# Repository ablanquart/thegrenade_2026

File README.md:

# The Grenade 2026 - An MRF101 40m AM Linear Amplifier
## USB-C Powered - 10W Carrier / 40W PEP - SMA Connectors

A bench-oriented 40-meter (7.0–7.3 MHz) AM linear amplifier built around a push-pull
pair of NXP **MRF101AN/MRF101BN** LDMOS transistors — powered from a standard 100 W
USB-C PD supply. Designed for experimental use under an FCC Part 5 license and
general amateur use on 40m.

**10 W carrier / 40 W PEP · 50 Ω in/out · runs from a laptop brick · absorptive harmonic termination**

## Features

- **USB-C powered**: negotiates 20 V / 5 A from any 100 W PD supply via a CH224K sink
  controller, then boosts to 48 V with an LM5122 synchronous boost converter.
- **Dual power path**: the boost output and a 48 V bench input are diode-ORed onto the
  main VDD rail — plug in whichever you have; both is fine.
- **Absorptive harmonic termination**: a high-pass diplexer branch dumps everything the
  output low-pass filter rejects into a 50 Ω / 6 W resistive load instead of reflecting
  it back into the PA drains. The transistors see a resistive load at all frequencies.
- **Interlocked bring-up**: the driver supply (LM2596HV buck) is enabled only after PD
  negotiation succeeds, or manually via a force-enable jumper (J5).
- **Status LEDs**: green = PD negotiated and boost alive; amber = main 48 V rail present.
- Temperature-tracked gate bias for the output pair.
- 7-element Chebyshev low-pass output filter, 7.5 MHz cutoff.

## Repository layout

```
├── mrf101_40m_pa_usbpd.kicad_pro   # KiCad project
├── mrf101_40m_pa_usbpd.kicad_sch   # Schematic
├── mrf101_40m_pa_usbpd.kicad_pcb   # Board (220 × 130 mm, 2-layer)
├── BOM_mrf101_40m_pa_usbpd.csv     # Bill of materials (grouped, with quantities)
├── fab_usbpd/                      # Gerbers, drill files, paste layers
├── docs/
│   ├── USER_GUIDE.md               # Setup and operation
│   └── SERVICE_MANUAL.md           # Theory of operation, component reference, test points
├── CHANGELOG.md
├── LICENSE                         # CERN-OHL-S v2
└── README.md
```

## Quick start

1. Bolt the board to a heatsink — the MRF101 pair **requires** one (TO-220 tab-down).
2. Connect a 50 Ω dummy load or antenna system to **J2 (RF OUT)**. Never key without a load.
3. Power: plug a 100 W USB-C PD supply into **J4**, or 48 V bench into **J3**.
4. Green LED (D7) = PD negotiated; amber LED (D8) = 48 V rail up.
5. Apply drive (≈1 W nominal) to **J1 (RF IN)**.

Full setup, bias adjustment, and first-power-up procedures are in
[docs/USER_GUIDE.md](docs/USER_GUIDE.md). Circuit theory, a complete component function
reference, and oscilloscope test points are in
[docs/SERVICE_MANUAL.md](docs/SERVICE_MANUAL.md).

## Bill of materials

The complete grouped BOM is [`BOM_mrf101_40m_pa_usbpd.csv`](BOM_mrf101_40m_pa_usbpd.csv).
Sourcing notes for the parts that matter:

| Part | Refs | Notes |
|---|---|---|
| MRF101AN + MRF101BN | Q1, Q2 | Buy the AN/BN *pair* — mirrored pinouts for layout symmetry. |
| CH224K | U3 | USB-PD sink controller, SSOP-10. |
| LM5122 | U4 | Sync boost controller, HTSSOP-20 (exposed pad). |
| LM2596HV-12 | U2 | HV variant is mandatory — input is 48 V. |
| BN-43-202, BN-43-3312 | T1, T2 | Binocular ferrite cores; wind per schematic. |
| 330 pF C0G **250 V** | C33, C34 | Diplexer series caps — voltage rating matters. |
| 390 nH, Q > 50 @ 20 MHz | L8 | 1812 air-core/ceramic, or wind 8t on a T37-6. |
| 100 Ω **3 W** 2512 | R34, R35 | The harmonic dump — do not substitute smaller. |
| USB-C 16-pin receptacle | J4 | Mid-mount, 5 A rated. |

## Regenerating fabrication files

With KiCad 10.x:

```sh
KCLI=/Applications/KiCad/KiCad.app/Contents/MacOS/kicad-cli   # adjust for your OS

$KCLI pcb export gerbers mrf101_40m_pa_usbpd.kicad_pcb -o fab_usbpd/
$KCLI pcb export drill   mrf101_40m_pa_usbpd.kicad_pcb -o fab_usbpd/ \
      --excellon-units mm --excellon-separate-th
```

Include the paste layers (F.Paste/B.Paste) if you're having a stencil made.

## Safety

This is a 40-watt RF power amplifier running on a 48-volt rail. Treat it accordingly:
hot heatsinks, RF voltage on exposed copper, and enough stored energy in the bulk
capacitors to be memorable. Operate into a proper load, within your license privileges,
and keep fingers off the output network while transmitting.

## License

This project is licensed under the **CERN Open Hardware Licence Version 2 —
Strongly Reciprocal (CERN-OHL-S v2)**. See [LICENSE](LICENSE) for the full text.

Copyright © 2026 Adam Blanquart

This source describes Open Hardware and is licensed under the CERN-OHL-S v2.
You may redistribute and modify this source and make products using it under
the terms of the CERN-OHL-S v2 (https://ohwr.org/cern_ohl_s_v2.txt).

This source is distributed WITHOUT ANY EXPRESS OR IMPLIED WARRANTY, INCLUDING
OF MERCHANTABILITY, SATISFACTORY QUALITY AND FITNESS FOR A PARTICULAR PURPOSE.
Please see the CERN-OHL-S v2 for applicable conditions.

Source location: https://github.com/ablanquart/thegrenade_2026/

As per CERN-OHL-S v2 section 4.1, any product you make from this design should
carry a reference back to the source location above.

---

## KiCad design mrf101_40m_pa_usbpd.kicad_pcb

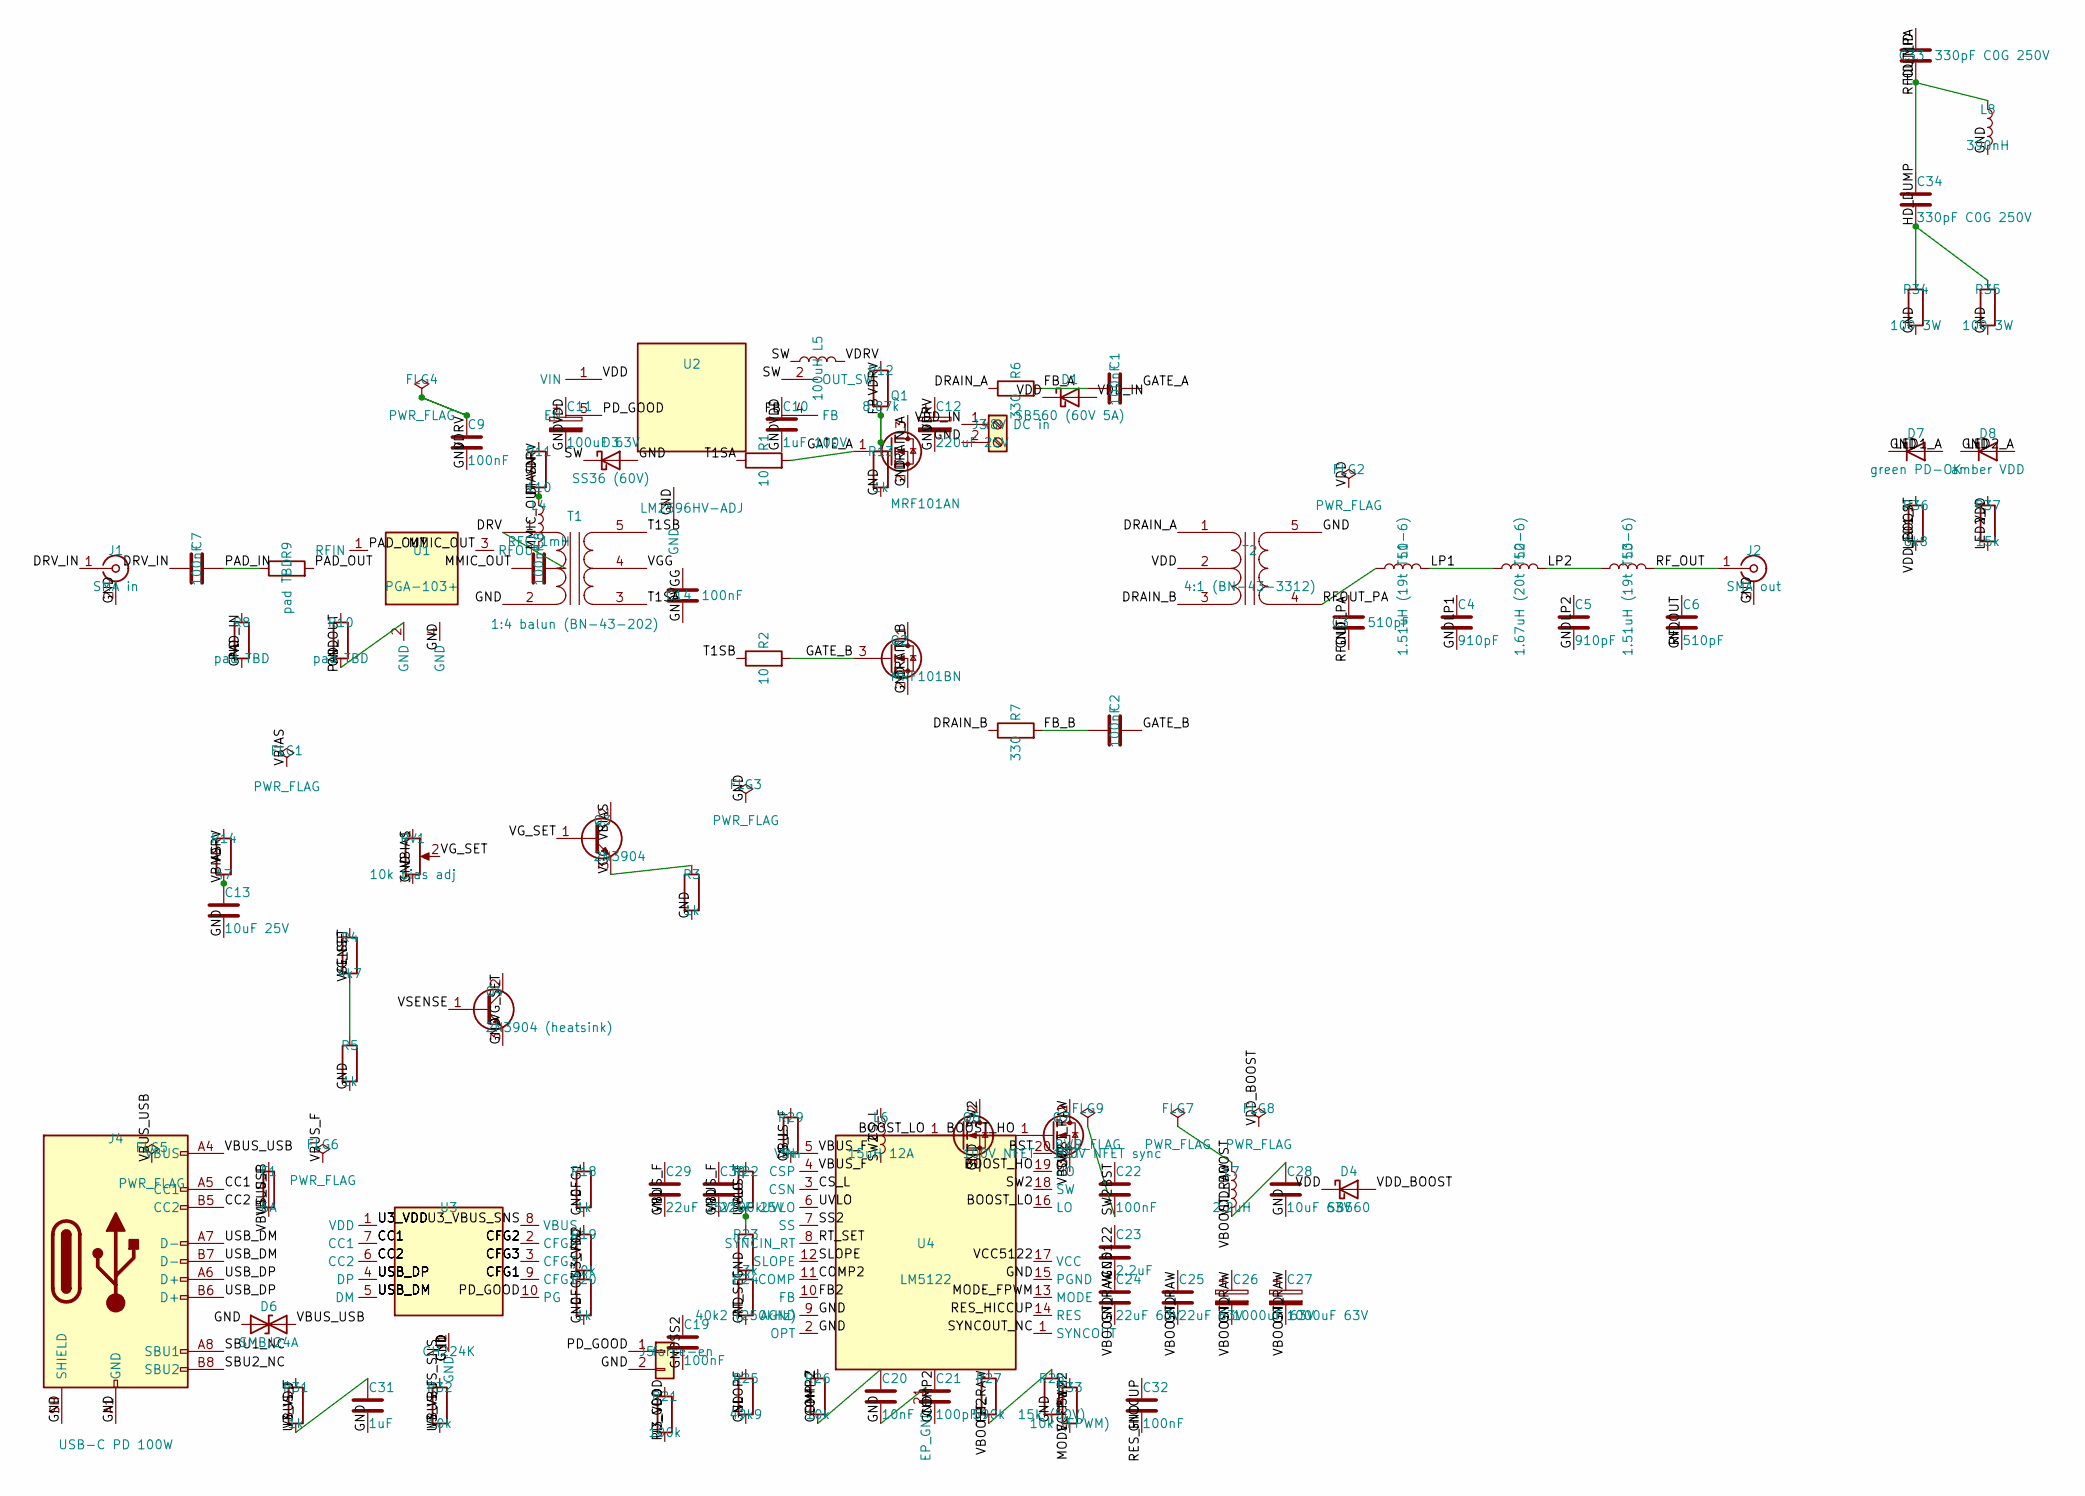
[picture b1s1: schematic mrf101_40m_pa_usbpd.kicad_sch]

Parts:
C1, C2, C7, C8, C9, C14, C19, C22, C32: 100nF; C_0805_2012Metric
C3, C6: 510pF; C_1206_3216Metric
C4, C5: 910pF; C_1206_3216Metric
C10: 1uF 100V; C_1206_3216Metric
C11: 100uF 63V; CP_Radial_D8.0mm_P3.50mm
C12: 220uF 25V; CP_Radial_D8.0mm_P3.50mm
C13: 10uF 25V; C_1206_3216Metric
C20: 10nF; C_0805_2012Metric
C21: 100pF; C_0805_2012Metric
C23: 2.2uF; C_1206_3216Metric
C24, C25: 22uF 63V; C_1210_3225Metric
C26, C27: 1000uF 63V; CP_Radial_D10.0mm_P5.00mm
C28: 10uF 63V; C_1210_3225Metric
C29, C30: 22uF 25V; C_1210_3225Metric
C31: 1uF; C_0805_2012Metric
C33, C34: 330pF C0G 250V; C_1210_3225Metric
D1: SB560 (60V 5A); D_SMC
D3: SS36 (60V); D_SMA
D4: SB560; D_SMC
D6: SMBJ24A; D_SMB
D7: green PD-OK; LED_0805_2012Metric
D8: amber VDD; LED_0805_2012Metric
F1: 6A; Fuse_1812_4532Metric
FLG1, FLG2, FLG3, FLG4, FLG5, FLG6, FLG7, FLG8, FLG9: PWR_FLAG
J1: SMA in; SMA_Molex_73251-1153_EdgeMount_Horizontal
J2: SMA out; SMA_Molex_73251-1153_EdgeMount_Horizontal
J3: 48V DC in; TerminalBlock_MaiXu_MX126-5.0-02P_1x02_P5.00mm
J4: USB-C PD 100W; USB_C_Receptacle_HRO_TYPE-C-31-M-12
J5: force-en; PinHeader_1x02_P2.54mm_Vertical
L1, L3: 1.51uH (19t T50-6); L_Toroid_Vertical_L14.0mm_W6.3mm_P4.57mm_Pulse_A
L2: 1.67uH (20t T50-6); L_Toroid_Vertical_L14.0mm_W6.3mm_P4.57mm_Pulse_A
L4: RFC 1mH; L_Toroid_Vertical_L14.0mm_W6.3mm_P4.57mm_Pulse_A
L5: 100uH; L_12x12mm_H8mm
L6: 15uH 12A; L_12x12mm_H8mm
L7: 2.2uH; L_12x12mm_H4.5mm
L8: 390nH; L_1812_4532Metric
Q1: MRF101AN; TO-220-3_Horizontal_TabDown
Q2: MRF101BN; TO-220-3_Horizontal_TabDown
Q3: 2N3904; TO-92_Inline
Q4: 2N3904 (heatsink); TO-92_Inline
Q6: 100V NFET; TO-252-2
Q7: 100V NFET sync; TO-252-2
R1, R2: 10; R_0805_2012Metric
R3, R5, R13, R18, R20, R31: 1k; R_0805_2012Metric
R4: 4k7; R_0805_2012Metric
R6, R7: 330; R_2512_6332Metric
R8, R9, R10: pad TBD; R_0805_2012Metric
R11: 110; R_0805_2012Metric
R12: 8.87k; R_0805_2012Metric
R14: 47; R_0805_2012Metric
R19, R26, R32: 10k; R_0805_2012Metric
R21, R22: 100k; R_0805_2012Metric
R23: 13k; R_0805_2012Metric
R24: 40k2 (250kHz); R_0805_2012Metric
R25: 49k9; R_0805_2012Metric
R27: 590k; R_0805_2012Metric
R28: 15k (50V); R_0805_2012Metric
R29: 5m; R_2512_6332Metric
R33: 10k (FPWM); R_0805_2012Metric
R34, R35: 100 3W; R_2512_6332Metric
R36: 6k8; R_0805_2012Metric
R37: 15k; R_1206_3216Metric
RV1: 10k bias adj; Potentiometer_Bourns_3296W_Vertical
T1: 1:4 balun (BN-43-202); Xfmr_Binocular_BN43-202_5pin
T2: 4:1 (BN-43-3312); Xfmr_Binocular_BN43-3312_5pin
U1: PGA-103+; PGA_103_MMIC
U2: LM2596HV-ADJ; TO-220-5_Vertical
U3: CH224K; SSOP-10-1EP_3.9x4.9mm_P1mm_EP2.1x3.3mm
U4: LM5122; HTSSOP-20-1EP_4.4x6.5mm_P0.65mm_EP3.4x6.5mm

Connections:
BIASN: L4.1, R11.2
BOOST_HO: Q7.1 (G), U4.19 (HO)
BOOST_LO: Q6.1 (G), U4.16 (LO)
BST: C22.1, U4.20 (BST)
CC1: J4.A5 (CC1), U3.7 (CC1)
CC2: J4.B5 (CC2), U3.6 (CC2)
CFG1: R18.1, U3.9 (CFG1)
CFG2: R19.1, U3.2 (CFG2)
CFG3: R20.1, U3.3 (CFG3)
COMP2: C21.1, R26.1, U4.11 (COMP)
COMP_Z: C20.1, R26.2
CS_L: L6.1, R29.2, U4.3 (CSN)
DRAIN_A: Q1.3 (D), R6.1, T2.1 (PR1)
DRAIN_B: Q2.1 (D), R7.1, T2.3 (PR2)
DRV: C8.2, T1.1 (AA)
DRV_IN: C7.1, J1.1 (In)
FB: R12.2, R13.1, U2.4 (FB)
FB2: R27.2, R28.1, U4.10 (FB)
FB_A: C1.1, R6.2
FB_B: C2.1, R7.2
GATE_A: C1.2, Q1.1 (G), R1.2
GATE_B: C2.2, Q2.3 (G), R2.2
GND: C3.2, C4.2, C5.2, C6.2, C9.2, C10.2, C11.2, C12.2, C13.2, C14.2, C19.2, C20.2, C21.2, C23.2, C24.2, C25.2, C26.2, C27.2, C28.2, C29.2, C30.2, C31.2, C32.2, D3.2 (A), D6.1 (A1), D7.1 (K), D8.1 (K), FLG3.1, J1.2 (Ext), J2.2 (Ext), J3.2, J4.A1 (GND), J4.A12 (GND), J4.B1 (GND), J4.B12 (GND), J4.SH (SHIELD), J5.2, L8.2, Q1.2 (S), Q2.2 (S), Q4.3 (E), Q6.3 (S), R3.2, R5.2, R8.2, R10.2, R13.2, R18.2, R20.2, R23.2, R24.2, R25.2, R28.2, R34.2, R35.2, RV1.3, T1.2 (AB), T2.5 (S2), U1.2 (GND), U1.4 (GND), U2.3 (GND), U3.11 (GND), U4.2 (OPT), U4.9 (AGND), U4.15 (PGND), U4.21 (EP_GND)
HD_DUMP: C34.2, R34.1, R35.1
HD_MID: C33.2, C34.1, L8.1
LED1_A: D7.2 (A), R36.2
LED2_A: D8.2 (A), R37.2
LP1: C4.1, L1.2, L2.1
LP2: C5.1, L2.2, L3.1
MMIC_OUT: C8.1, L4.2, U1.3 (RFOUT)
MODE_FPWM: R33.1, U4.13 (MODE)
PAD_IN: C7.2, R8.1, R9.1
PAD_OUT: R9.2, R10.1, U1.1 (RFIN)
PD_GOOD: J5.1, R21.2, U2.5 (EN), U3.10 (PG)
RES_HICCUP: C32.1, U4.14 (RES)
RFOUT_PA: C3.1, C33.1, L1.1, T2.4 (S1)
RF_OUT: C6.1, J2.1 (In), L3.2
RT_SET: R24.1, U4.8 (SYNCIN_RT)
SBU1_NC: J4.A8 (SBU1)
SBU2_NC: J4.B8 (SBU2)
SLOPE: R25.1, U4.12 (SLOPE)
SS2: C19.1, U4.7 (SS)
SW: D3.1 (K), L5.1, U2.2 (OUT_SW)
SW2: C22.2, FLG9.1, L6.2, Q6.2 (D), Q7.3 (S), U4.18 (SW)
SYNCOUT_NC: U4.1 (SYNCOUT)
T1SA: R1.1, T1.3 (SA)
T1SB: R2.1, T1.5 (SB)
U3_VBUS_SNS: R32.2, U3.8 (VBUS)
U3_VDD: C31.1, R19.2, R21.1, R31.2, U3.1 (VDD)
USB_DM: J4.A7 (D-), J4.B7 (D-), U3.5 (DM)
USB_DP: J4.A6 (D+), J4.B6 (D+), U3.4 (DP)
UVLO: R22.2, R23.1, U4.6 (UVLO)
VBIAS: C13.1, FLG1.1, Q3.2 (C), R14.2, RV1.1
VBOOST_RAW: C24.1, C25.1, C26.1, C27.1, FLG7.1, L7.1, Q7.2 (D), R27.1
VBUS_F: C29.1, C30.1, F1.2, FLG6.1, R22.1, R29.1, R31.1, R32.1, U4.4 (CSP), U4.5 (VIN)
VBUS_USB: D6.2 (A2), F1.1, FLG5.1, J4.A4 (VBUS), J4.A9 (VBUS), J4.B4 (VBUS), J4.B9 (VBUS)
VCC5122: C23.1, R33.2, U4.17 (VCC)
VDD: C10.1, C11.1, D1.1 (K), D4.1 (K), FLG2.1, R37.1, T2.2 (PM), U2.1 (VIN)
VDD_BOOST: C28.1, D4.2 (A), FLG8.1, L7.2, R36.1
VDD_IN: D1.2 (A), J3.1
VDRV: C9.1, C12.1, FLG4.1, L5.2, R11.1, R12.1, R14.1
VGG: C14.1, Q3.3 (E), R3.1, T1.4 (SC)
VG_SET: Q3.1 (B), Q4.2 (C), R4.1, RV1.2
VSENSE: Q4.1 (B), R4.2, R5.1

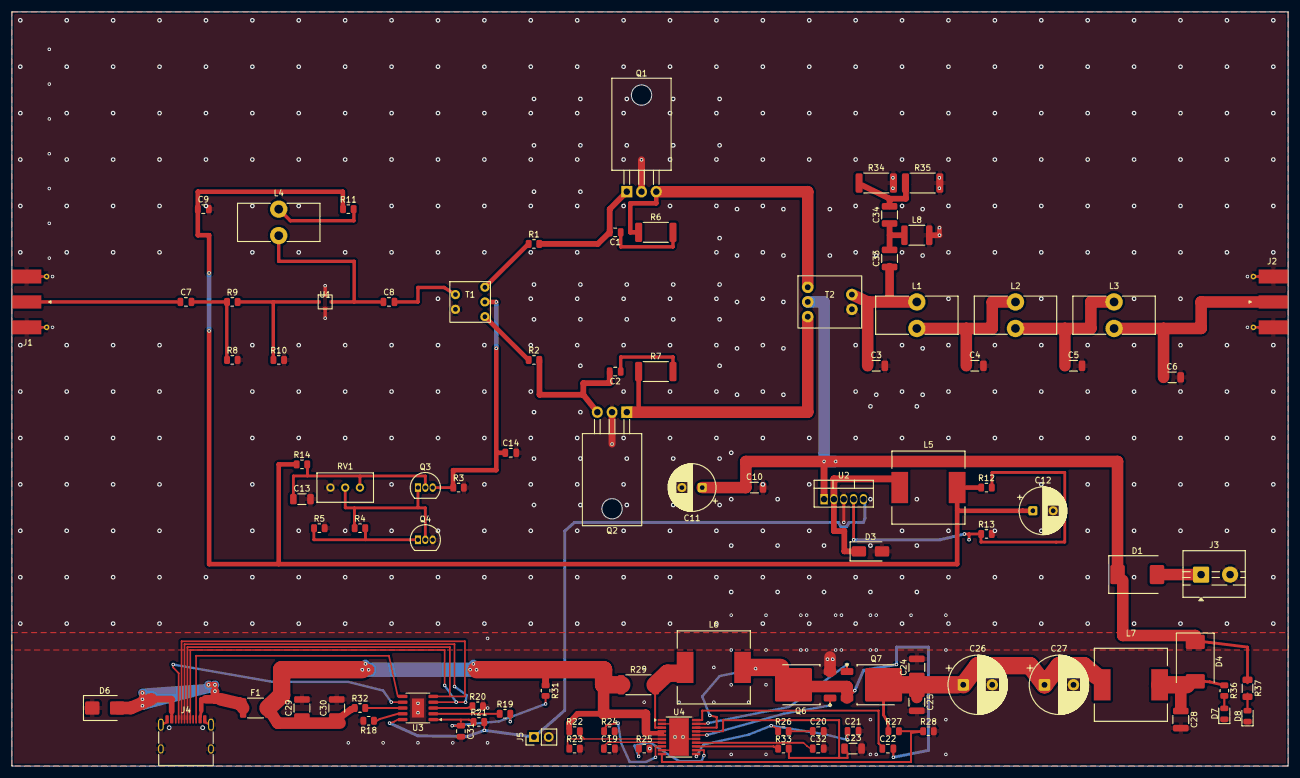
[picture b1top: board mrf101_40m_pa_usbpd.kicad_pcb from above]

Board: 2 copper layers, 220.0 x 130.0 mm, 96 parts (0 on the bottom side), 61 nets.

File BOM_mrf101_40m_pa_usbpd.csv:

"Refs","Value","Footprint","Qty"
"C1,C2,C7-C9,C14,C19,C22,C32","100nF","Capacitor_SMD:C_0805_2012Metric","9"
"C3,C6","510pF","Capacitor_SMD:C_1206_3216Metric","2"
"C4,C5","910pF","Capacitor_SMD:C_1206_3216Metric","2"
"C10","1uF 100V","Capacitor_SMD:C_1206_3216Metric","1"
"C11","100uF 63V","Capacitor_THT:CP_Radial_D8.0mm_P3.50mm","1"
"C12","220uF 25V","Capacitor_THT:CP_Radial_D8.0mm_P3.50mm","1"
"C13","10uF 25V","Capacitor_SMD:C_1206_3216Metric","1"
"C20","10nF","Capacitor_SMD:C_0805_2012Metric","1"
"C21","100pF","Capacitor_SMD:C_0805_2012Metric","1"
"C23","2.2uF","Capacitor_SMD:C_1206_3216Metric","1"
"C24,C25","22uF 63V","Capacitor_SMD:C_1210_3225Metric","2"
"C26,C27","1000uF 63V","Capacitor_THT:CP_Radial_D10.0mm_P5.00mm","2"
"C28","10uF 63V","Capacitor_SMD:C_1210_3225Metric","1"
"C29,C30","22uF 25V","Capacitor_SMD:C_1210_3225Metric","2"
"C31","1uF","Capacitor_SMD:C_0805_2012Metric","1"
"C33,C34","330pF C0G 250V","Capacitor_SMD:C_1210_3225Metric","2"
"D1","SB560 (60V 5A)","Diode_SMD:D_SMC","1"
"D3","SS36 (60V)","Diode_SMD:D_SMA","1"
"D4","SB560","Diode_SMD:D_SMC","1"
"D6","SMBJ24A","Diode_SMD:D_SMB","1"
"D7","green PD-OK","LED_SMD:LED_0805_2012Metric","1"
"D8","amber VDD","LED_SMD:LED_0805_2012Metric","1"
"F1","6A","Fuse:Fuse_1812_4532Metric","1"
"FLG1-FLG9","PWR_FLAG","","9"
"J1","SMA in","Connector_Coaxial:SMA_Molex_73251-1153_EdgeMount_Horizontal","1"
"J2","SMA out","Connector_Coaxial:SMA_Molex_73251-1153_EdgeMount_Horizontal","1"
"J3","48V DC in","TerminalBlock:TerminalBlock_MaiXu_MX126-5.0-02P_1x02_P5.00mm","1"
"J4","USB-C PD 100W","Connector_USB:USB_C_Receptacle_HRO_TYPE-C-31-M-12","1"
"J5","force-en","Connector_PinHeader_2.54mm:PinHeader_1x02_P2.54mm_Vertical","1"
"L1,L3","1.51uH (19t T50-6)","Inductor_THT:L_Toroid_Vertical_L14.0mm_W6.3mm_P4.57mm_Pulse_A","2"
"L2","1.67uH (20t T50-6)","Inductor_THT:L_Toroid_Vertical_L14.0mm_W6.3mm_P4.57mm_Pulse_A","1"
"L4","RFC 1mH","Inductor_THT:L_Toroid_Vertical_L14.0mm_W6.3mm_P4.57mm_Pulse_A","1"
"L5","100uH","Inductor_SMD:L_12x12mm_H8mm","1"
"L6","15uH 12A","Inductor_SMD:L_12x12mm_H8mm","1"
"L7","2.2uH","Inductor_SMD:L_12x12mm_H4.5mm","1"
"L8","390nH","Inductor_SMD:L_1812_4532Metric","1"
"Q1","MRF101AN","Package_TO_SOT_THT:TO-220-3_Horizontal_TabDown","1"
"Q2","MRF101BN","Package_TO_SOT_THT:TO-220-3_Horizontal_TabDown","1"
"Q3","2N3904","Package_TO_SOT_THT:TO-92_Inline","1"
"Q4","2N3904 (heatsink)","Package_TO_SOT_THT:TO-92_Inline","1"
"Q6","100V NFET","Package_TO_SOT_SMD:TO-252-2","1"
"Q7","100V NFET sync","Package_TO_SOT_SMD:TO-252-2","1"
"R1,R2","10","Resistor_SMD:R_0805_2012Metric","2"
"R3,R5,R13,R18,R20,R31","1k","Resistor_SMD:R_0805_2012Metric","6"
"R4","4k7","Resistor_SMD:R_0805_2012Metric","1"
"R6,R7","330","Resistor_SMD:R_2512_6332Metric","2"
"R8-R10","pad TBD","Resistor_SMD:R_0805_2012Metric","3"
"R11","110","Resistor_SMD:R_0805_2012Metric","1"
"R12","8.87k","Resistor_SMD:R_0805_2012Metric","1"
"R14","47","Resistor_SMD:R_0805_2012Metric","1"
"R19,R26,R32","10k","Resistor_SMD:R_0805_2012Metric","3"
"R21,R22","100k","Resistor_SMD:R_0805_2012Metric","2"
"R23","13k","Resistor_SMD:R_0805_2012Metric","1"
"R24","40k2 (250kHz)","Resistor_SMD:R_0805_2012Metric","1"
"R25","49k9","Resistor_SMD:R_0805_2012Metric","1"
"R27","590k","Resistor_SMD:R_0805_2012Metric","1"
"R28","15k (50V)","Resistor_SMD:R_0805_2012Metric","1"
"R29","5m","Resistor_SMD:R_2512_6332Metric","1"
"R33","10k (FPWM)","Resistor_SMD:R_0805_2012Metric","1"
"R34,R35","100 3W","Resistor_SMD:R_2512_6332Metric","2"
"R36","6k8","Resistor_SMD:R_0805_2012Metric","1"
"R37","15k","Resistor_SMD:R_1206_3216Metric","1"
"RV1","10k bias adj","Potentiometer_THT:Potentiometer_Bourns_3296W_Vertical","1"
"T1","1:4 balun (BN-43-202)","linear_amp:Xfmr_Binocular_BN43-202_5pin","1"
"T2","4:1 (BN-43-3312)","linear_amp:Xfmr_Binocular_BN43-3312_5pin","1"
"U1","PGA-103+","linear_amp:PGA_103_MMIC","1"
"U2","LM2596HV-ADJ","Package_TO_SOT_THT:TO-220-5_Vertical","1"
"U3","CH224K","Package_SO:SSOP-10-1EP_3.9x4.9mm_P1mm_EP2.1x3.3mm","1"
"U4","LM5122","Package_SO:HTSSOP-20-1EP_4.4x6.5mm_P0.65mm_EP3.4x6.5mm","1"
